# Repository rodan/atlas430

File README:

reference libraries for projects that use the MSP430 microcontroller.

 homepage:        https://github.com/rodan/reference_libs_msp430
 author:          Petre Rodan <2b4eda@subdimension.ro>
 license:         BSD

 contains drivers for the following:

 * driverlib
  - TI MSP430 DriverLib (provided as git submodule)

 * glue
  - i2c with blocking implementation based on the TI DriverLib
  - i2c controlled by interrupts (IRQ_I2C)
  - bitbanged i2c
  - uart with optional interrupt driven tx
  - system messagebus
  - ring buffer

 * drivers
  - Honeywell High Accuracy Ceramic (HSC) and Standard Accuracy Ceramic (SSC) piezoresistive silicon pressure sensors
  - Sensirion SHT 1x humidity and temperature sensors
  - Maxim DS3231 rtc IC
  - Maxim DS3234 rtc IC
  - Analog Devices AD7789 adc IC
  - Cypress FM24* i2c FRAM IC
  - Texas Instruments TCA6408 IO expander 

 * tests
  - a Makefile driven collection of unit tests for different drivers

 * tools
  - generic script for flashing uCs

 software requirements:

	msp430 toolchain
	make
	Linux OS (for makefile scripts). might work with WSL or cygwin, not tested.

	tested on a stable Gentoo Linux system with Mitto Systems GCC 9.3.1.1-based toolchain

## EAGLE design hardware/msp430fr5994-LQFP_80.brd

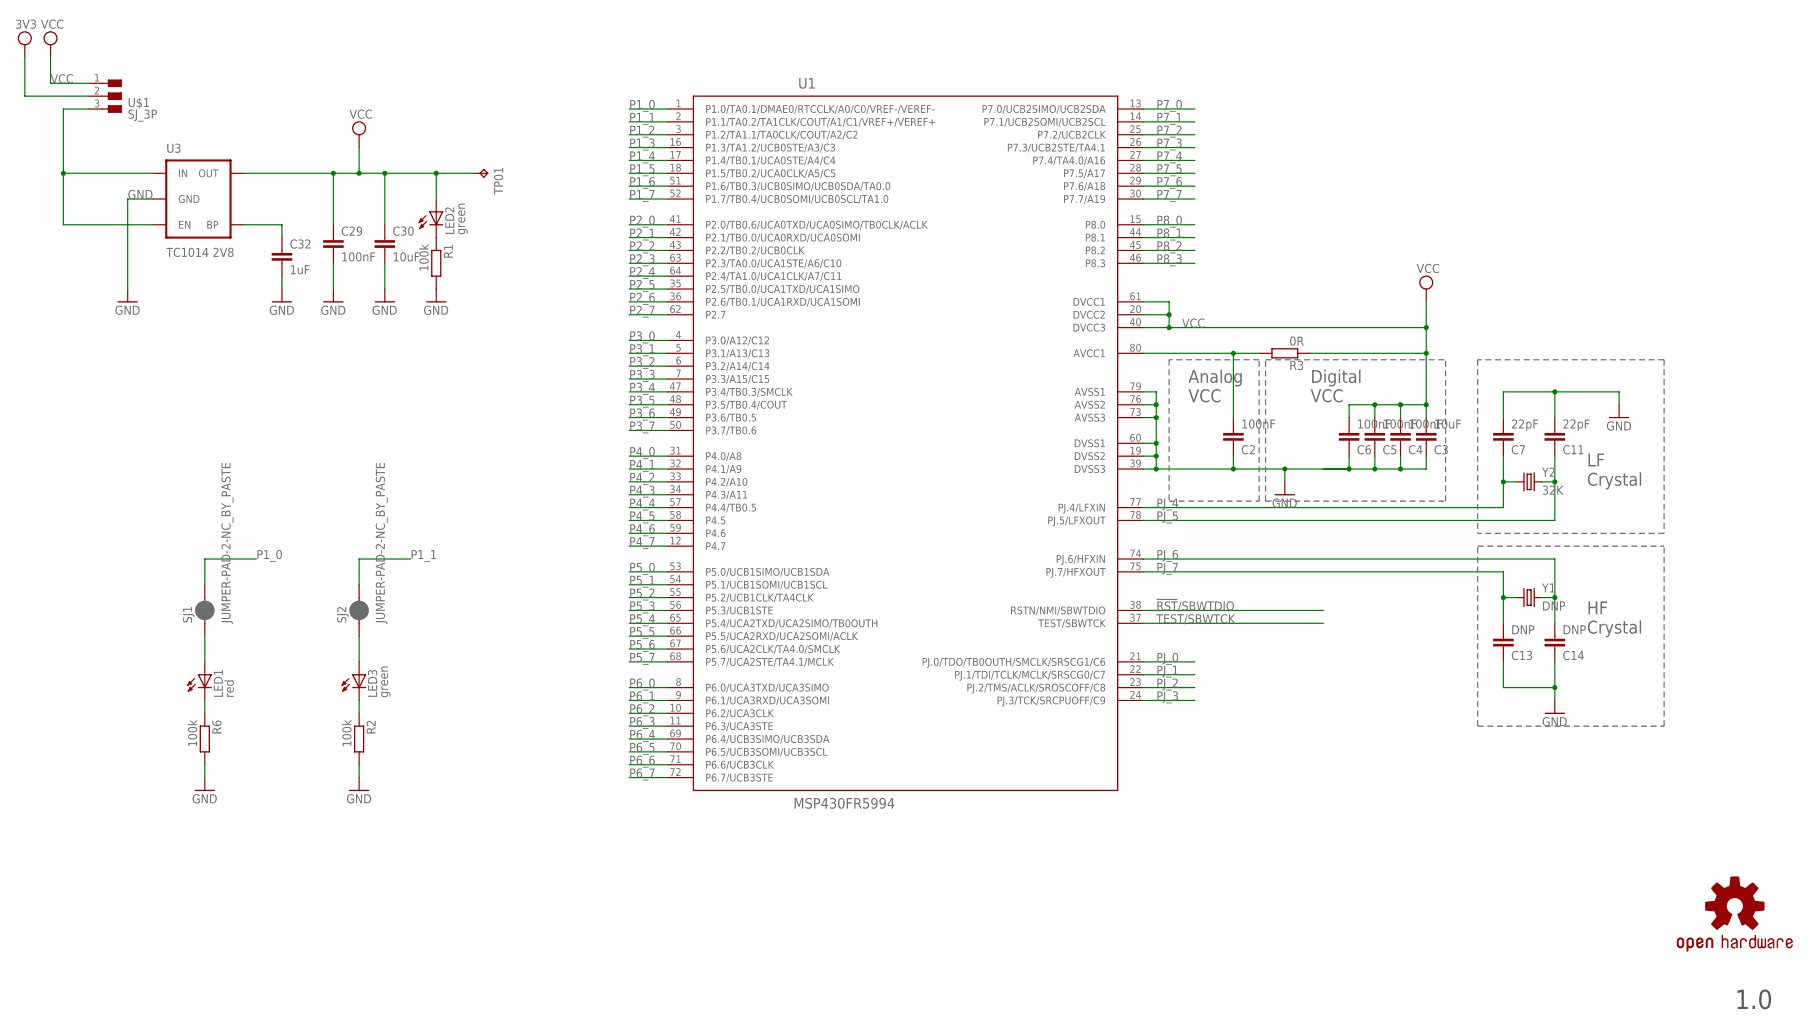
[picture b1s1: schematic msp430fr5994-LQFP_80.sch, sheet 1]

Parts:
C2, C4, C5, C6, C29: 100nF; C0805
C3: 10uF; C0805
C7, C11: 22pF; C0805
C13, C14: DNP; C0805
C30: 10uF; C1206
C32: 1uF; C0805
LED1: red; CHIPLED_0805
LED2, LED3: green; CHIPLED_0805
R1, R2, R6: 100k; R0805W
R3: 0R; R0805W
SJ1, SJ2: JUMPER-PAD-2-NC_BY_PASTE; PAD-JUMPER-2-NC_BY_PASTE_YES_SILK
TP01: TPTP12R; TP12R
U1: MSP430FR5994; PN80
U3: TC1014 2V8; SOT23-5
U$1: SJ_3P
U$7: OSHW-LOGOM; OSHW-LOGO-M
Y1: DNP; CRYSTAL-SMD-11.4X4.35
Y2: 32K; CRYSTAL-SMD-3.2X1.5

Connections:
3V3: U$1.2; also elsewhere on the board
!RST!/SBWTDIO: U1.38 (RSTN/NMI/SBWTDIO); also elsewhere on the board
GND: C2.1, C3.1, C4.1, C5.1, C6.1, C7.2, C11.2, C13.1, C14.1, C29.2, C30.2, C32.2, R1.2, R2.2, R6.2, U1.19 (DVSS2), U1.39 (DVSS3), U1.60 (DVSS1), U1.73 (AVSS3), U1.76 (AVSS2), U1.79 (AVSS1), U3.2 (GND); also elsewhere on the board
unnamed: U3.1 (IN), U3.3 (EN), U$1.3
unnamed: C2.2, R3.2, U1.80 (AVCC1)
unnamed: LED2.C, R1.1
unnamed: LED1.A, SJ1.1
unnamed: LED3.C, R2.1
unnamed: LED3.A, SJ2.1
unnamed: LED1.C, R6.1
unnamed: C32.1, U3.4 (BP)
P1_0: SJ1.2, U1.1 (P1.0/TA0.1/DMAE0/RTCCLK/A0/C0/VREF-/VER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); also elsewhere on the board
P1_1: SJ2.2, U1.2 (P1.1/TA0.2/TA1CLK/COUT/A1/C1/VREF+/VERE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); also elsewhere on the board
P1_2: U1.3 (P1.2/TA1.1/TA0CLK/COUT/A2/C2); also elsewhere on the board
P1_3: U1.16 (P1.3/TA1.2/UCB0STE/A3/C3); also elsewhere on the board
P1_4: U1.17 (P1.4/TB0.1/UCA0STE/A4/C4); also elsewhere on the board
P1_5: U1.18 (P1.5/TB0.2/UCA0CLK/A5/C5); also elsewhere on the board
P1_6: U1.51 (P1.6/TB0.3/UCB0SIMO/UCB0SDA/TA0.0); also elsewhere on the board
P1_7: U1.52 (P1.7/TB0.4/UCB0SOMI/UCB0SCL/TA1.0); also elsewhere on the board
P2_0: U1.41 (P2.0/TB0.6/UCA0TXD/UCA0SIMO/TB0CLK/ACLK); also elsewhere on the board
P2_1: U1.42 (P2.1/TB0.0/UCA0RXD/UCA0SOMI); also elsewhere on the board
P2_2: U1.43 (P2.2/TB0.2/UCB0CLK); also elsewhere on the board
P2_3: U1.63 (P2.3/TA0.0/UCA1STE/A6/C10); also elsewhere on the board
P2_4: U1.64 (P2.4/TA1.0/UCA1CLK/A7/C11); also elsewhere on the board
P2_5: U1.35 (P2.5/TB0.0/UCA1TXD/UCA1SIMO); also elsewhere on the board
P2_6: U1.36 (P2.6/TB0.1/UCA1RXD/UCA1SOMI); also elsewhere on the board
P2_7: U1.62 (P2.7); also elsewhere on the board
P3_0: U1.4 (P3.0/A12/C12); also elsewhere on the board
P3_1: U1.5 (P3.1/A13/C13); also elsewhere on the board
P3_2: U1.6 (P3.2/A14/C14); also elsewhere on the board
P3_3: U1.7 (P3.3/A15/C15); also elsewhere on the board
P3_4: U1.47 (P3.4/TB0.3/SMCLK); also elsewhere on the board
P3_5: U1.48 (P3.5/TB0.4/COUT); also elsewhere on the board
P3_6: U1.49 (P3.6/TB0.5); also elsewhere on the board
P3_7: U1.50 (P3.7/TB0.6); also elsewhere on the board
P4_0: U1.31 (P4.0/A8); also elsewhere on the board
P4_1: U1.32 (P4.1/A9); also elsewhere on the board
P4_2: U1.33 (P4.2/A10); also elsewhere on the board
P4_3: U1.34 (P4.3/A11); also elsewhere on the board
P4_4: U1.57 (P4.4/TB0.5); also elsewhere on the board
P4_5: U1.58 (P4.5); also elsewhere on the board
P4_6: U1.59 (P4.6); also elsewhere on the board
P4_7: U1.12 (P4.7); also elsewhere on the board
P5_0: U1.53 (P5.0/UCB1SIMO/UCB1SDA); also elsewhere on the board
P5_1: U1.54 (P5.1/UCB1SOMI/UCB1SCL); also elsewhere on the board
P5_2: U1.55 (P5.2/UCB1CLK/TA4CLK); also elsewhere on the board
P5_3: U1.56 (P5.3/UCB1STE); also elsewhere on the board
P5_4: U1.65 (P5.4/UCA2TXD/UCA2SIMO/TB0OUTH); also elsewhere on the board
P5_5: U1.66 (P5.5/UCA2RXD/UCA2SOMI/ACLK); also elsewhere on the board
P5_6: U1.67 (P5.6/UCA2CLK/TA4.0/SMCLK); also elsewhere on the board
P5_7: U1.68 (P5.7/UCA2STE/TA4.1/MCLK); also elsewhere on the board
P6_0: U1.8 (P6.0/UCA3TXD/UCA3SIMO); also elsewhere on the board
P6_1: U1.9 (P6.1/UCA3RXD/UCA3SOMI); also elsewhere on the board
P6_2: U1.10 (P6.2/UCA3CLK); also elsewhere on the board
P6_3: U1.11 (P6.3/UCA3STE); also elsewhere on the board
P6_4: U1.69 (P6.4/UCB3SIMO/UCB3SDA); also elsewhere on the board
P6_5: U1.70 (P6.5/UCB3SOMI/UCB3SCL); also elsewhere on the board
P6_6: U1.71 (P6.6/UCB3CLK); also elsewhere on the board
P6_7: U1.72 (P6.7/UCB3STE); also elsewhere on the board
P7_0: U1.13 (P7.0/UCB2SIMO/UCB2SDA); also elsewhere on the board
P7_1: U1.14 (P7.1/UCB2SOMI/UCB2SCL); also elsewhere on the board
P7_2: U1.25 (P7.2/UCB2CLK); also elsewhere on the board
P7_3: U1.26 (P7.3/UCB2STE/TA4.1); also elsewhere on the board
P7_4: U1.27 (P7.4/TA4.0/A16); also elsewhere on the board
P7_5: U1.28 (P7.5/A17); also elsewhere on the board
P7_6: U1.29 (P7.6/A18); also elsewhere on the board
P7_7: U1.30 (P7.7/A19); also elsewhere on the board
P8_0: U1.15 (P8.0); also elsewhere on the board
P8_1: U1.44 (P8.1); also elsewhere on the board
P8_2: U1.45 (P8.2); also elsewhere on the board
P8_3: U1.46 (P8.3); also elsewhere on the board
PJ_0: U1.21 (PJ.0/TDO/TB0OUTH/SMCLK/SRSCG1/C6); also elsewhere on the board
PJ_1: U1.22 (PJ.1/TDI/TCLK/MCLK/SRSCG0/C7); also elsewhere on the board
PJ_2: U1.23 (PJ.2/TMS/ACLK/SROSCOFF/C8); also elsewhere on the board
PJ_3: U1.24 (PJ.3/TCK/SRCPUOFF/C9); also elsewhere on the board
PJ_4: C7.1, U1.77 (PJ.4/LFXIN), Y2.P$1 (1)
PJ_5: C11.1, U1.78 (PJ.5/LFXOUT), Y2.P$2 (2)
PJ_6: C14.2, U1.74 (PJ.6/HFXIN), Y1.2
PJ_7: C13.2, U1.75 (PJ.7/HFXOUT), Y1.1
TEST/SBWTCK: U1.37 (TEST/SBWTCK); also elsewhere on the board
VCC: C3.2, C4.2, C5.2, C6.2, C29.1, C30.1, LED2.A, R3.1, TP01.TP, U1.20 (DVCC2), U1.40 (DVCC3), U1.61 (DVCC1), U3.5 (OUT), U$1.1; also elsewhere on the board

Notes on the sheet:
1.0
Analog
VCC
Digital
Crystal

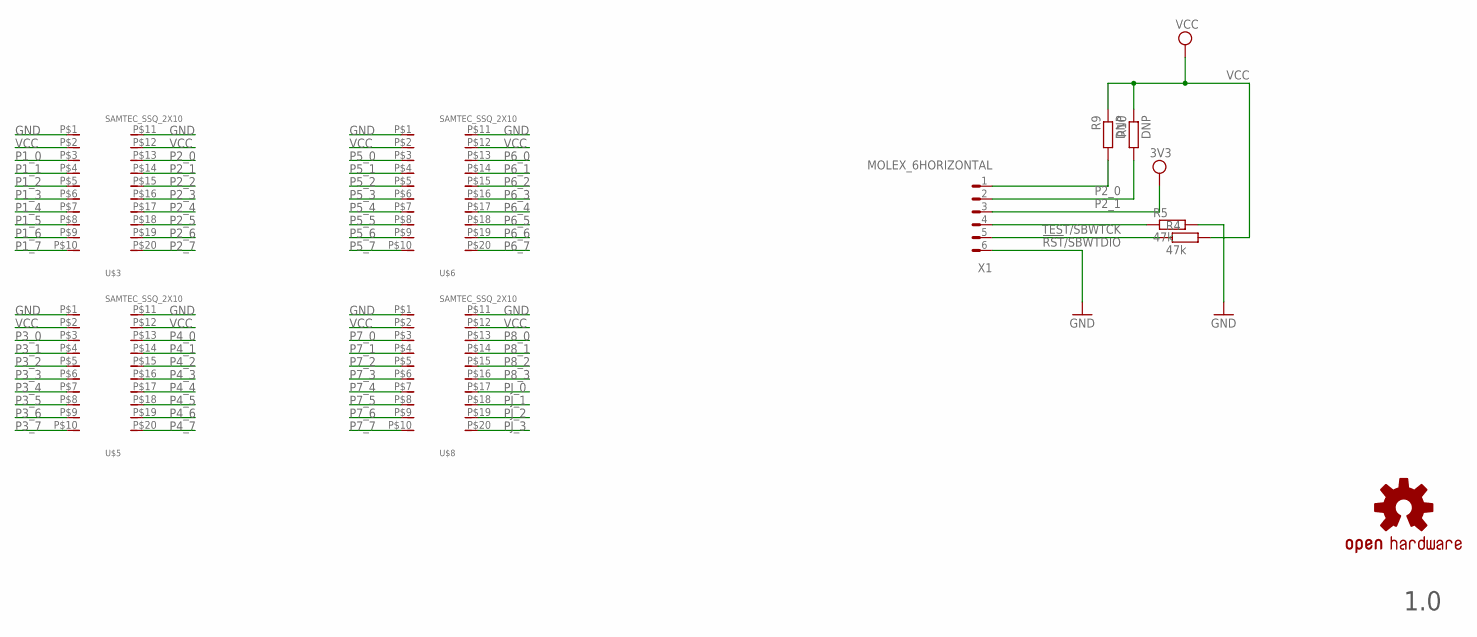
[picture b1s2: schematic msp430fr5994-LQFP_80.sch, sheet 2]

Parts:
R4, R5: 47k; R0805W
R9, R10: DNP; R0805W
U$2: OSHW-LOGOM; OSHW-LOGO-M
U$3, U$5, U$6, U$8: SAMTEC_SSQ_2X10; SSQ-110-03-G-D
X1: MOLEX_6HORIZONTAL; 0530480610

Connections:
3V3: X1.3 (4); also elsewhere on the board
!RST!/SBWTDIO: R4.1, X1.5 (2); also elsewhere on the board
GND: R5.2, U$3.P$1, U$3.P$11, U$5.P$1, U$5.P$11, U$6.P$1, U$6.P$11, U$8.P$1, U$8.P$11, X1.6 (1); also elsewhere on the board
P1_0: U$3.P$3; also elsewhere on the board
P1_1: U$3.P$4; also elsewhere on the board
P1_2: U$3.P$5; also elsewhere on the board
P1_3: U$3.P$6; also elsewhere on the board
P1_4: U$3.P$7; also elsewhere on the board
P1_5: U$3.P$8; also elsewhere on the board
P1_6: U$3.P$9; also elsewhere on the board
P1_7: U$3.P$10; also elsewhere on the board
P2_0: R9.2, U$3.P$13, X1.1 (6); also elsewhere on the board
P2_1: R10.2, U$3.P$14, X1.2 (5); also elsewhere on the board
P2_2: U$3.P$15; also elsewhere on the board
P2_3: U$3.P$16; also elsewhere on the board
P2_4: U$3.P$17; also elsewhere on the board
P2_5: U$3.P$18; also elsewhere on the board
P2_6: U$3.P$19; also elsewhere on the board
P2_7: U$3.P$20; also elsewhere on the board
P3_0: U$5.P$3; also elsewhere on the board
P3_1: U$5.P$4; also elsewhere on the board
P3_2: U$5.P$5; also elsewhere on the board
P3_3: U$5.P$6; also elsewhere on the board
P3_4: U$5.P$7; also elsewhere on the board
P3_5: U$5.P$8; also elsewhere on the board
P3_6: U$5.P$9; also elsewhere on the board
P3_7: U$5.P$10; also elsewhere on the board
P4_0: U$5.P$13; also elsewhere on the board
P4_1: U$5.P$14; also elsewhere on the board
P4_2: U$5.P$15; also elsewhere on the board
P4_3: U$5.P$16; also elsewhere on the board
P4_4: U$5.P$17; also elsewhere on the board
P4_5: U$5.P$18; also elsewhere on the board
P4_6: U$5.P$19; also elsewhere on the board
P4_7: U$5.P$20; also elsewhere on the board
P5_0: U$6.P$3; also elsewhere on the board
P5_1: U$6.P$4; also elsewhere on the board
P5_2: U$6.P$5; also elsewhere on the board
P5_3: U$6.P$6; also elsewhere on the board
P5_4: U$6.P$7; also elsewhere on the board
P5_5: U$6.P$8; also elsewhere on the board
P5_6: U$6.P$9; also elsewhere on the board
P5_7: U$6.P$10; also elsewhere on the board
P6_0: U$6.P$13; also elsewhere on the board
P6_1: U$6.P$14; also elsewhere on the board
P6_2: U$6.P$15; also elsewhere on the board
P6_3: U$6.P$16; also elsewhere on the board
P6_4: U$6.P$17; also elsewhere on the board
P6_5: U$6.P$18; also elsewhere on the board
P6_6: U$6.P$19; also elsewhere on the board
P6_7: U$6.P$20; also elsewhere on the board
P7_0: U$8.P$3; also elsewhere on the board
P7_1: U$8.P$4; also elsewhere on the board
P7_2: U$8.P$5; also elsewhere on the board
P7_3: U$8.P$6; also elsewhere on the board
P7_4: U$8.P$7; also elsewhere on the board
P7_5: U$8.P$8; also elsewhere on the board
P7_6: U$8.P$9; also elsewhere on the board
P7_7: U$8.P$10; also elsewhere on the board
P8_0: U$8.P$13; also elsewhere on the board
P8_1: U$8.P$14; also elsewhere on the board
P8_2: U$8.P$15; also elsewhere on the board
P8_3: U$8.P$16; also elsewhere on the board
PJ_0: U$8.P$17; also elsewhere on the board
PJ_1: U$8.P$18; also elsewhere on the board
PJ_2: U$8.P$19; also elsewhere on the board
PJ_3: U$8.P$20; also elsewhere on the board
TEST/SBWTCK: R5.1, X1.4 (3); also elsewhere on the board
VCC: R4.2, R9.1, R10.1, U$3.P$2, U$3.P$12, U$5.P$2, U$5.P$12, U$6.P$2, U$6.P$12, U$8.P$2, U$8.P$12; also elsewhere on the board

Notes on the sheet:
1.0

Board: 2 copper layers, 38 parts (4 on the bottom side), 81 nets, no tracks yet.

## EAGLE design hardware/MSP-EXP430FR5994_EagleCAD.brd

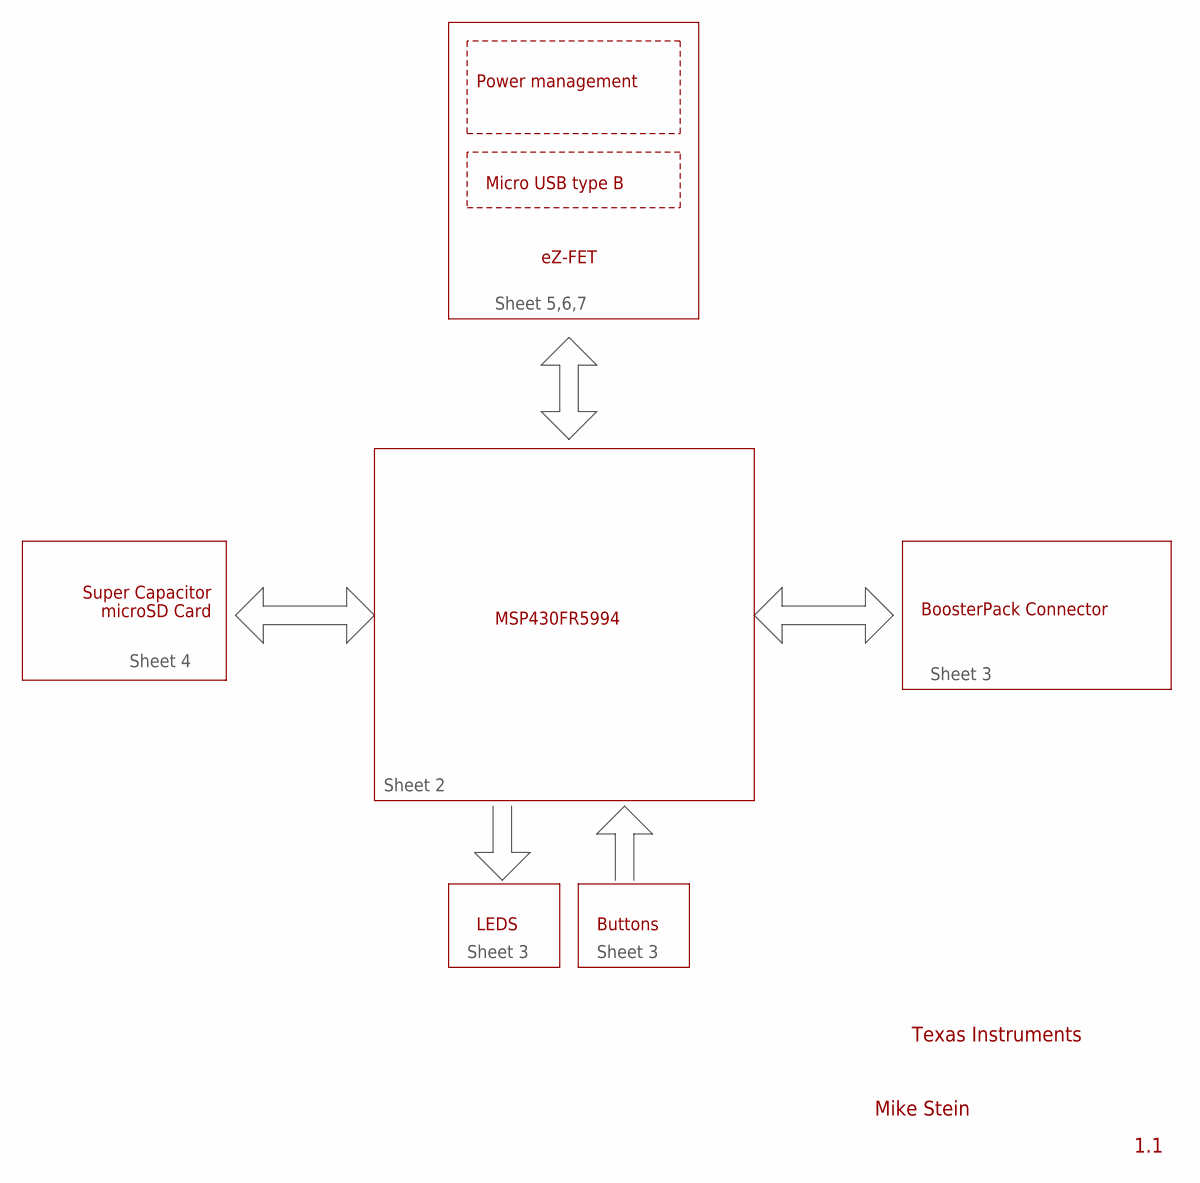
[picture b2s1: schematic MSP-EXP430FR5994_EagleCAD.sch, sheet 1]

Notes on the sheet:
Power management
Micro USB type B
eZ-FET
MSP430FR5994
BoosterPack Connector
LEDS
Buttons
Sheet 2
Sheet 5,6,7
Sheet 3
Texas Instruments
Super Capacitor
Sheet 4
microSD Card

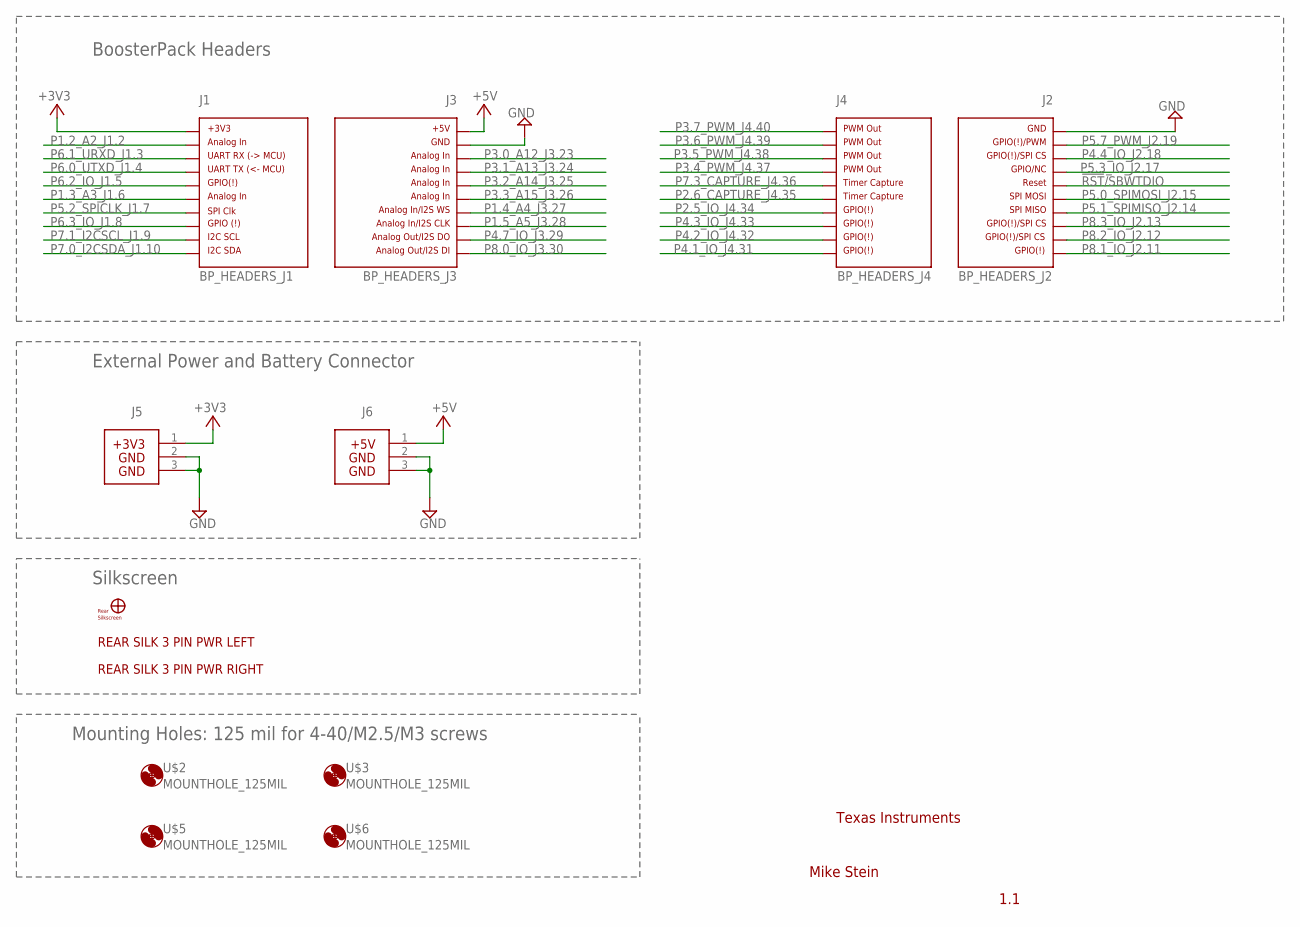
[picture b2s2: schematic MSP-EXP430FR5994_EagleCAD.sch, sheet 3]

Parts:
J1: BP_HEADERS_J1; J1
J2: BP_HEADERS_J2; J2
J3: BP_HEADERS_J3; J3
J4: BP_HEADERS_J4; J4
J5: HEADER 1X03; 3PIN_PWR_3V3
J6: BP_HEADERS_PWR_5V; 3PIN_PWR_5V
U$1: FR5994_REARSILK_REV1_0
U$2, U$3, U$5, U$6: MOUNTHOLE_125MIL
U$7: MIKE_TM
U$8: BP_3PIN_SILK; 3PIN_PWR_SILK
U$10: BP_3PIN_SILK_RT; 3PIN_PWR_SILK_RT

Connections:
!RST!/SBWTDIO: J2.16
+3V3: J1.1, J5.1
+5V: J3.21, J6.1
P1.2_A2_J1.2: J1.2
P1.3_A3_J1.6: J1.6
P1.4_A4_J3.27: J3.27
P1.5_A5_J3.28: J3.28
P2.5_IO_J4.34: J4.34
P2.6_CAPTURE_J4.35: J4.35
P3.0_A12_J3.23: J3.23
P3.1_A13_J3.24: J3.24
P3.2_A14_J3.25: J3.25
P3.3_A15_J3.26: J3.26
P3.4_PWM_J4.37: J4.37
P3.5_PWM_J4.38: J4.38
P3.6_PWM_J4.39: J4.39
P3.7_PWM_J4.40: J4.40
P4.1_IO_J4.31: J4.31
P4.2_IO_J4.32: J4.32
P4.3_IO_J4.33: J4.33
P4.4_IO_J2.18: J2.18
P4.7_IO_J3.29: J3.29
P5.0_SPIMOSI_J2.15: J2.15
P5.1_SPIMISO_J2.14: J2.14
P5.2_SPICLK_J1.7: J1.7
P5.3_IO_J2.17: J2.17
P5.7_PWM_J2.19: J2.19
P6.0_UTXD_J1.4: J1.4
P6.1_URXD_J1.3: J1.3
P6.2_IO_J1.5: J1.5
P6.3_IO_J1.8: J1.8
P7.0_I2CSDA_J1.10: J1.10
P7.1_I2CSCL_J1.9: J1.9
P7.3_CAPTURE_J4.36: J4.36
P8.0_IO_J3.30: J3.30
P8.1_IO_J2.11: J2.11
P8.2_IO_J2.12: J2.12
P8.3_IO_J2.13: J2.13
TGT_GND: J2.20, J3.22, J5.2, J5.3, J6.2, J6.3

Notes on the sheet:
Mounting Holes: 125 mil for 4-40/M2.5/M3 screws
BoosterPack Headers
External Power and Battery Connector
Silkscreen
Texas Instruments

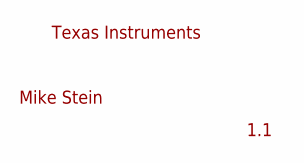
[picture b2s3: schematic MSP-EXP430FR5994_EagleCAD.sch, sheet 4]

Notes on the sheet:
Texas Instruments

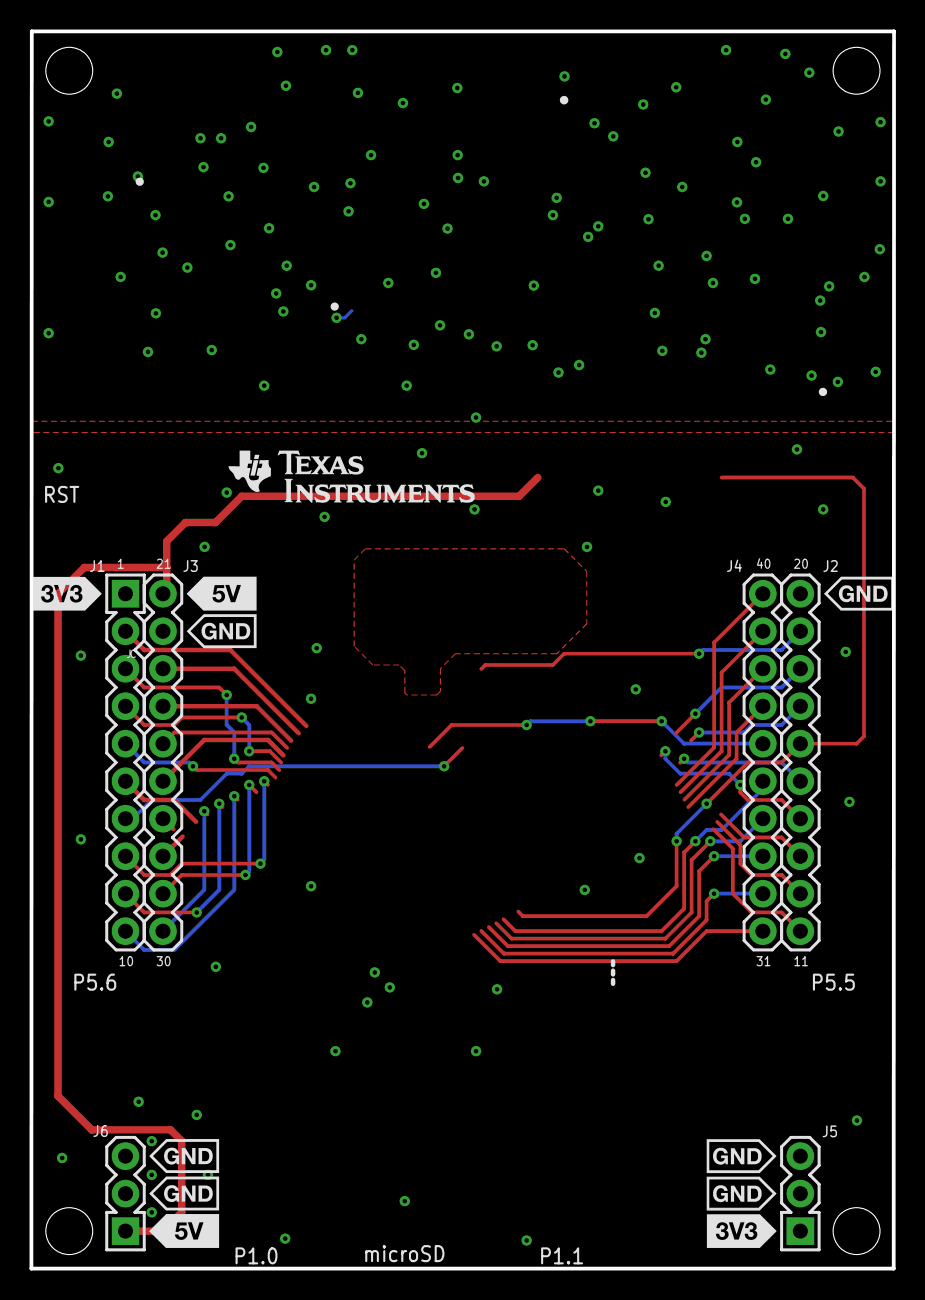
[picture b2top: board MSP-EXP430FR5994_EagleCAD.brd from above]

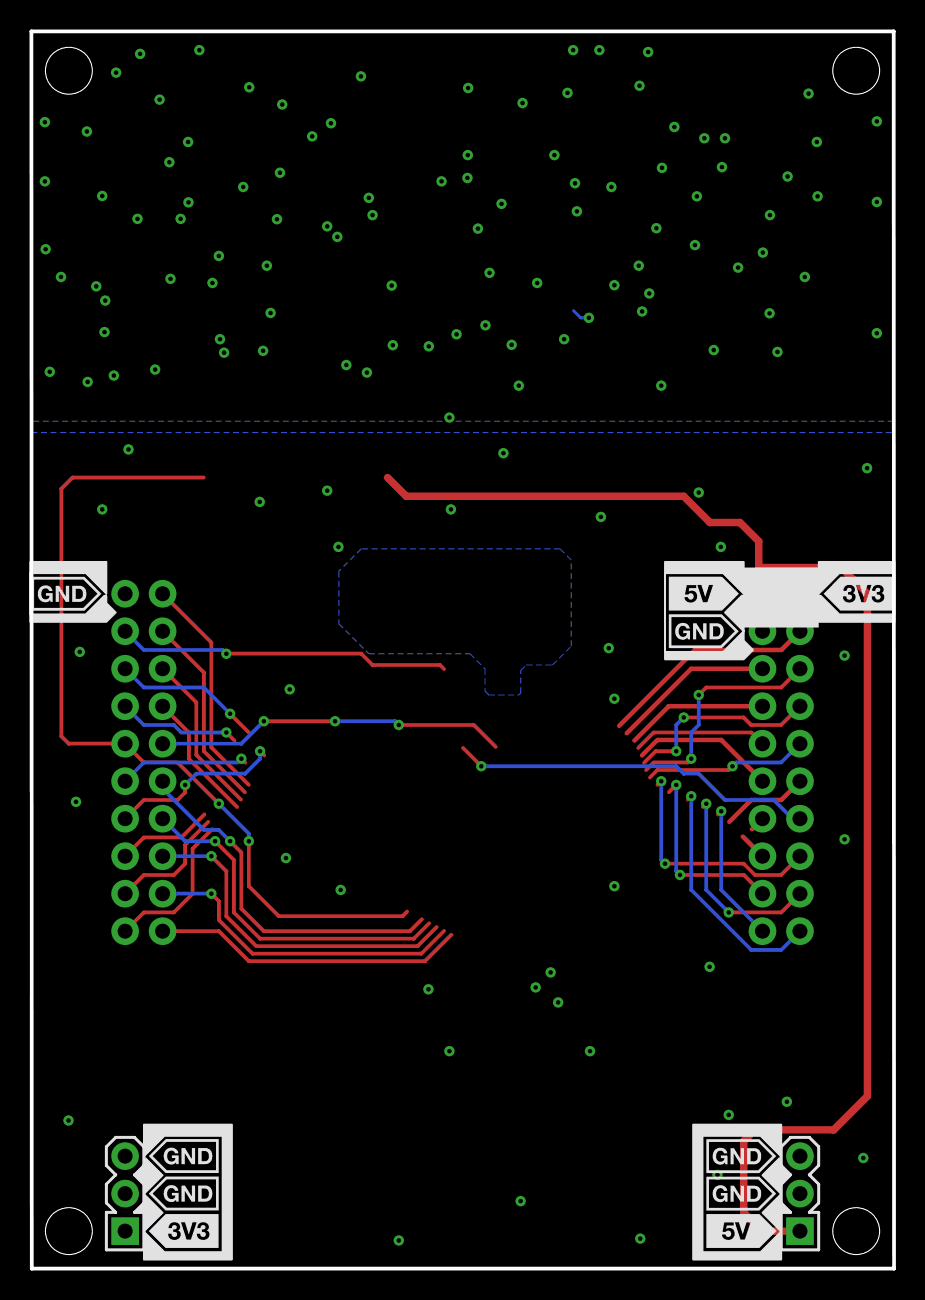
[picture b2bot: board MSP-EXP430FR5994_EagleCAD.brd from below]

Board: 4 copper layers, 58.4 x 83.8 mm, 17 parts (2 on the bottom side), 3 nets.

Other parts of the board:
DRAW1, DRAW3: LOGO-ROCKET-10X7MM-BRD
U$4: LOGO16_TPLACE

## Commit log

2013-12-02 add filtering
2013-12-17 use proper syntax to define the serial interface protocol
2014-01-20 add timer_a0 overflow counter
2014-01-27 add support for flash r/w, ads1110
2014-06-14 uart1 changes
2014-06-14 add i2c driver
2014-06-14 allow reads without the need of write
2014-06-14 add hardware i2c interface for hsc
2014-06-14 add own address for slave i2c
2014-06-14 fix NAK case
2014-06-23 add i2c slave driver
2015-08-27 add guides and rs485 lib
2015-10-30 add port map calculator
2015-11-10 i2c bitbang and sensirion update
2015-11-10 filter out true, false
2015-11-11 add more drivers
2018-09-01 email change
2019-01-12 fix CCR typo, add ADC temp reading
2019-01-13 latest
2019-01-14 add support for EUSCI-based i2c
2021-06-19 add tests
2021-06-19 add submodules
2021-06-19 add 5510 target
2021-06-19 Makefile targets are now ifdefs
2021-06-21 clock, uart1 working on 5510 5524
2021-06-21 add glue
2021-10-11 makefile updates
2021-10-11 remove modules
2021-10-11 add driverlib, glue
2021-10-31 Makefile cleanup
2021-11-02 glue moved to glue/generic, scripts updated
2021-11-02 add clock jitter test
2021-11-02 uart1 rewrite
2021-11-03 add linux setup checker, libmsp430.so
2021-11-03 provide error level if binaries are missing
2021-11-03 config.h cleanup
2021-11-05 uart cleanup
2021-11-08 uartX_tx() becomes blocking until ringbuf is full
2021-11-08 add uart2, uart3 to msp430f5xx and uart2 to msp430fr5xx
2021-11-08 add tests for uart2, uart3
2021-11-09 new readme
2021-11-09 new logo
2021-11-09 markdown testing
2021-11-09 make envcheck option added
2021-11-09 msp430_hal_init() now takes an argument
2021-11-09 start to populate glue/MSP430FR2xx
2021-11-11 uart init now errors out if baud not defined
2021-11-11 clock subsystem works for fr2355
2021-11-11 clock subsystem works for fr2433
2021-11-11 clock subsystem works for fr2476
2021-11-11 clock subsystem works for fr4133
2021-11-11 clock subsystem works for fr6989
2021-11-11 add libmsp430.so that comes with ccs
2021-11-11 cleanup
2021-11-11 added a few readmes
2021-11-12 add header tester
2021-11-12 add header
2021-11-12 clock subsystem works for fr5969
2021-11-12 clock subsystem works for all devboards
2021-11-12 add driverlib patch
2021-11-12 uart working on fr6989
2021-11-12 add PMM_unlockLPM5() to _hal_init()
2021-11-12 re-add buf to uart0/main.c
2021-11-13 remove MSP430F5438 support since it's EOL
2021-11-13 move doc files from root
2021-11-13 include generated Makefile.identify-target
2021-11-17 spec parser part 1 of many
2021-11-17 FR2xx-4xx crystal pins automatically generated
2021-11-18 cleanup gen_functions.sh
2021-11-19 parser ok for XIN XOUT, FR5xx_6xx, FR2xx_4xx
2021-11-19 parser cleanup
2021-11-20 parser ok for XIN XOUT, FR5xx_6xx, FR2xx_4xx, F5xx_6xx
2021-11-20 parser now understands dedicated pins
2021-11-22 add support for UCAxRXD/UCAxTXD datasheet parsing
2021-11-23 add uart parsing for FR2xx_4xx
2021-11-24 add uart parsing for F5xx_6xx
2021-11-24 parallel processing for pdf parsing functions
2021-11-25 uart_config added to fr5xx_6xx
2021-11-25 add devboards to readme
2021-11-25 uart testing begins
2021-11-25 uart test cleanup
2021-11-26 f5xx-6xx uart test passed
2021-11-26 fr5xx_6xx uart test passes
2021-11-26 fr2xx-4xx uart test passed
2021-11-29 clock table added
2021-11-29 project rename
2021-11-29 add uart pin map
2021-11-29 add compatibility table
2021-11-30 i2c datasheet parsing added
2021-12-01 generate pin not found #error s in generated code
2021-12-01 add i2c pins
2021-12-02 i2c testing part1
2021-12-02 i2c cleanup
2021-12-02 make i2c hardware implementation the default and add the optional I2C_USES_BITBANGING define
2021-12-02 hsc test working
2021-12-03 tests cleanup
2021-12-03 support for per-target i2c_config.h
2021-12-05 i2c bug fixed in USCI_B_I2C_masterReceiveMultiByteFinish()
2021-12-06 uart back channel mapper header added to unit test
2021-12-06 test with no irq
2021-12-08 all i2c tests pass
2021-12-08 remove 'under development' banner
2021-12-10 add ads1110 driver
2021-12-14 new project that uses atlas
2022-01-03 add spi parsing
2022-01-04 spi parsing added
2022-01-04 fix spi parsing errors
2022-01-05 spi files added
2022-01-07 test for a spi master implementation
2022-01-07 6989 spi_master working
2022-01-08 all ics except fr2433 works with spi_master
2022-01-08 all tests pass for spi_master
2022-01-08 add driver for Microchip MCP41xxx/MCP42xxx ic
2022-01-08 add driver for pga2311 ic
2022-01-09 uartX_pin functions converted to uart_ucaX_pin
2022-01-10 generic uart interface
2022-01-11 generic uart interface working with f5510, fr5994
2022-01-12 tests now use the new uart functionality
2022-01-12 fix cppcheck makefile target
2022-01-12 retest all boards with latest uart code, all tests passed
2022-01-12 remove per IC uart config - using generic config.h that activates all UART_USES_UCAx channels
2022-01-15 readme fix
2022-01-17 add uart documentation
2022-01-21 repair pedantic warnings
2022-03-11 add spi slave pin init support
2022-03-13 add new project to readme
2022-03-13 add guard
2022-05-02 i2c checks
2022-08-29 add exfiltration sample code
2023-01-22 add glue/generic scheduler with configurable timer baseaddress
2023-01-30 scheduler support tested on devboards part1
2023-01-31 added msp430f5438 devoboard tests
2024-02-06 Makefile: fix grep warning about stray '\'
2024-02-06 make LD path compatible with the atlas430 ebuild from my overlay project
2024-11-11 add FreeBSD support
2024-11-11 add libmsp430 libs
2024-11-14 add minicom wrapper script
2024-11-14 minicom_wrapper: retab
2024-12-17 - libatlas430.a static archive is generated during the build - path changes - static archive is created in separate Makefile
2024-12-18 sys -> arch move
2024-12-18 glue.h -> atlas430.h rename
2025-02-12 device model patch - part1
2025-02-12 device model patch - part2
2025-02-13 hbmps: cleanup
2025-02-14 dsrtc: rewrite part1
2025-02-16 dsrtc: implement rtc read
2025-02-16 dsrtc: cleanup
2025-02-17 dsrtc - i2c bus interaction tested
2025-02-19 libmsp430.so FreeBSD: remove libboost-* version-specific shared object dependency
2025-02-19 readme: typo
2025-02-21 bus: implementing i2c bitbanging part1
2025-02-24 tests/Makefile: add objdump disassemble target
2025-02-24 tests/Makefile: add debug_listen and scripted debug targets
2025-02-24 serial_bitbang: port and pin declarations are now function parameters instead of macros
2025-02-24 i2c bus: use bus status as lock, pack bus_read and bus_write into bus_transfer
2025-02-24 Makefile: remove accidental redirect during objdump target
2025-02-26 ads1110: switch to new bus API, add function description comments
2025-02-26 fm24: driver now uses the new bus API, bus: move slave_address from bus_spec to dev
2025-02-27 tests/i2c: re-add fm24 bitbang test using new bus API
2025-02-27 drivers/fm24: replace FM_LA macro with fm24_spec_t struct

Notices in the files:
hardware/MSP-EXP430FR5994_EagleCAD.brd:
(C)2003 A. DANNENBERG
parts and their libraries:
TI-LaunchPad-Eagle: As far as I know the LaunchPad rocket is released by TI under the Creative Commons license.
SparkFun-Passives: Licensing: Creative Commons ShareAlike 4.0 International - https://creativecommons.org/licenses/by-sa/4.0
